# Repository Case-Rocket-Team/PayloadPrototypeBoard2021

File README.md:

This is a prototype board for the 2021 ESRA Payload. We are planning on developing a parafoil guided payload that will be ejected from the rocket at apogee, and guide itself to landing. 

Capabilities of this board include: 
  6 Servo Outputs
  4 External IO 
  High Acceleration Accelerometer (H3LIS331DLTR)
  9 Axis IMU (ICM-20948) 
  LORA Radio (RFM98) 
  Barometer (BMP388) 
  18V Max Input
  Battery Voltage Reader
  Various LEDs for status 

This board should be used on the scale test payload we are developing, and will be a proof of concept for the final ESRA payload we will develop after validating this design.

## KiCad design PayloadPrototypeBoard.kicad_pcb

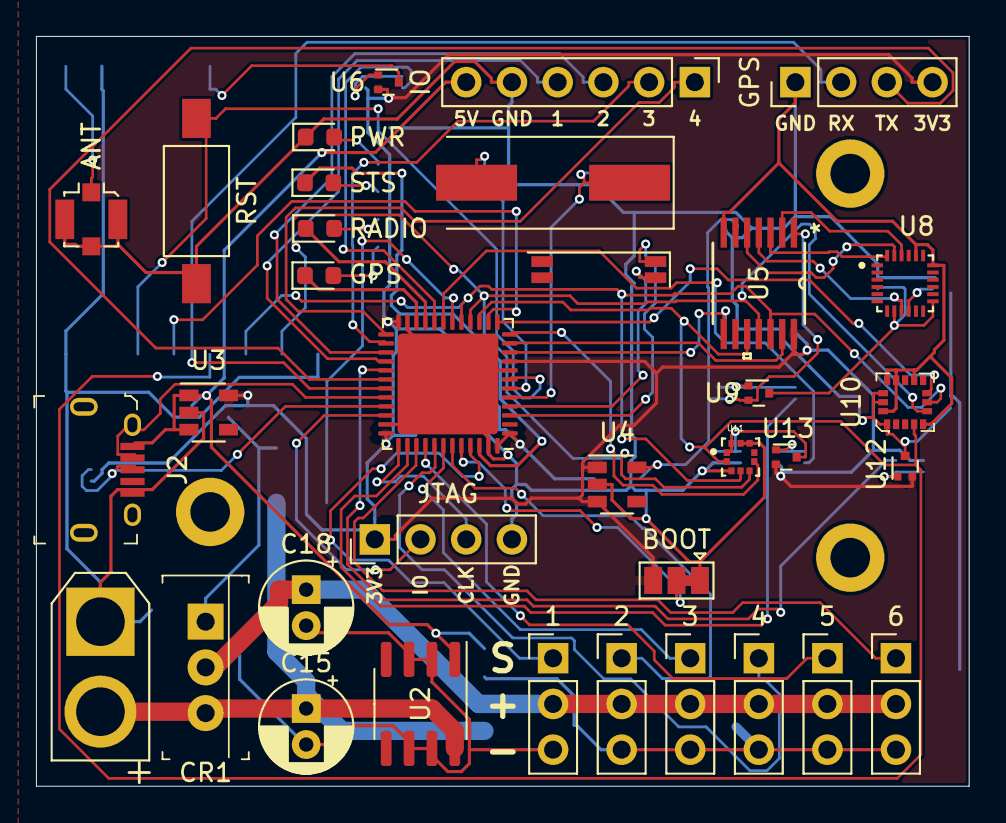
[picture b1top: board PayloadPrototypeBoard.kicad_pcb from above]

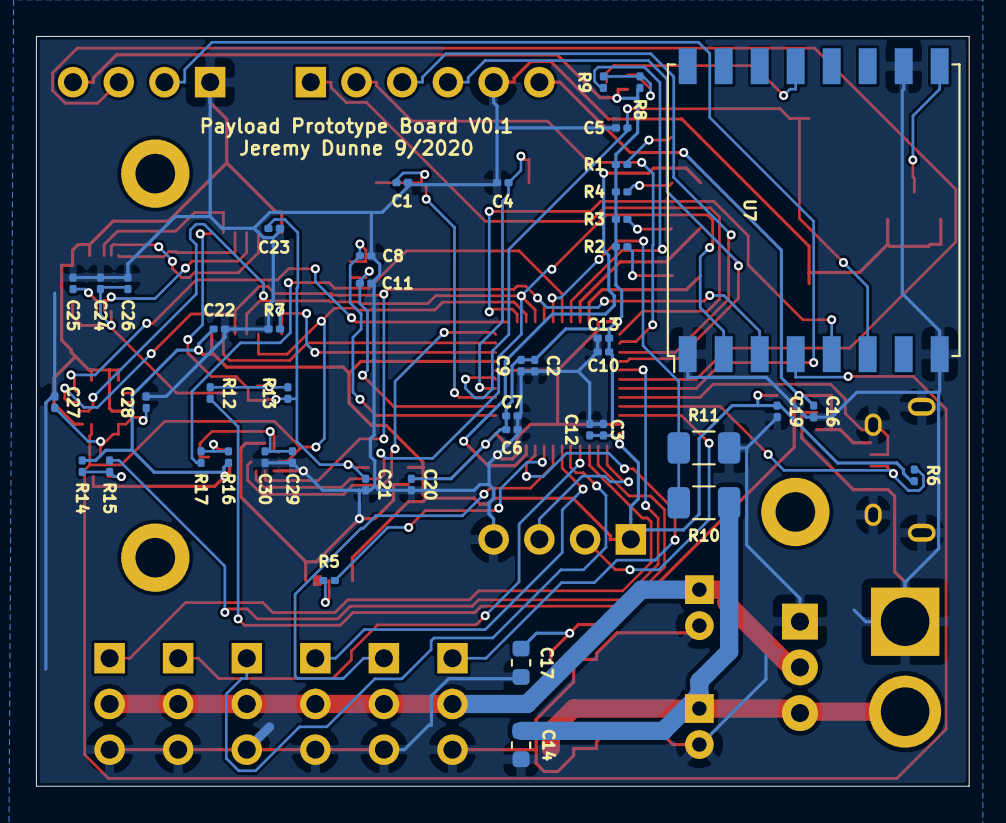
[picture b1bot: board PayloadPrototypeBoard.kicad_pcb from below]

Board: 2 copper layers, 51.8 x 41.7 mm, 84 parts (46 on the bottom side), 63 nets.

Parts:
1: SERVO 1; PinHeader_1x03_P2.54mm_Vertical
2: SERVO 2; PinHeader_1x03_P2.54mm_Vertical
3: SERVO 3; PinHeader_1x03_P2.54mm_Vertical
4: SERVO 4; PinHeader_1x03_P2.54mm_Vertical
5: SERVO 5; PinHeader_1x03_P2.54mm_Vertical
6: SERVO 6; PinHeader_1x03_P2.54mm_Vertical
ANT: Conn_Coaxial; U.FL_Molex_MCRF_73412-0110_Vertical
BOOT: BOOT0; SolderJumper-3_P1.3mm_Bridged12_Pad1.0x1.5mm
C1, C4: 20pF; C_0201_0603Metric
C2, C16, C19, C20, C21: 1uF; C_0201_0603Metric
C3: 10nF; C_0201_0603Metric
C5, C6, C9, C10, C12, C22, C23, C24, C25, C26, C29, C30: 0.1uF; C_0201_0603Metric
C7, C13: 4.7uF; C_0201_0603Metric
C8, C11: 10pF; C_0201_0603Metric
C14: 0.33uF; C_0603_1608Metric
C15, C18: 10uF; CP_Radial_D5.0mm_P2.00mm
C17: 0.1uF; C_0603_1608Metric
C27: 10uF; C_0201_0603Metric
C28: .1uF; C_0201_0603Metric
CR1: LD1085V50; TO-220-3
GPS: GPS_LOCK; LED_0603_1608Metric
GPS#2: GPS; PinHeader_1x04_P2.54mm_Vertical
H1, H2, H3: MountingHole; MountingHole_2.2mm_M2_DIN965_Pad
IO: EXTERNAL IO; PinHeader_1x06_P2.54mm_Vertical
J2: USB_OTG; USB_Micro_B_Female_10118194-0001LF
J9: PWR; AMASS_XT30U-F_1x02_P5.0mm_Vertical
JTAG: JTAG; PinHeader_1x04_P2.54mm_Vertical
PWR: PWR; LED_0603_1608Metric
R1, R2, R3, R4, R5, R7, R8, R9, R12, R13, R14, R15, R16, R17: 10K; R_0201_0603Metric
R6: 1.5K; R_0201_0603Metric
R10: 10K; R_1206_3216Metric
R11: 2.5k; R_1206_3216Metric
RADIO: RADIO_LOCK; LED_0603_1608Metric
RST: RESET; SW_SPST_FSMSM
STS: STATUS; LED_0603_1608Metric
U1: STM32F072C8Ux; QFN-48-1EP_7x7mm_P0.5mm_EP5.6x5.6mm
U2: L78L05_SO8; SOIC-8_3.9x4.9mm_P1.27mm
U3: MIC5504-3.3YM5; SOT-23-5
U4: MIC5504-1.8YM5; SOT-23-5
U5: TXS0104EPWR
U6, U9, U12, U13: SSM3J15FV; SOT-723
U7: RFM96W-433S2; HOPERF_RFM9XW_SMD
U8: ICM-20948; QFN40P300X300X105-24N
U10: H3LIS331DLTR; TFLGA-16_3x3mm
U11: BMP388; PQFN50P200X200X80-10N
Y1: 8MHz; Crystal_SMD_HC49-SD
Y2: 32Khz; Crystal_SMD_SeikoEpson_MC146-4Pin_6.7x1.5mm

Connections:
+1V8: C21.1, C23.2, R13.1, U4.5, U5.1, U9.2
+3V3: BOOT.3, C2.1, C3.1, C6.1, C7.1, C9.1, C10.1, C12.1, C13.1, C19.1, C20.1, C22.1, GPS#2.4, JTAG.1, R1.2, R2.2, R3.2, R4.2, R6.2, R8.2, R14.1, R16.2, U1.1, U1.9, U1.24, U1.36, U1.48, U3.5, U4.1, U4.3, U5.14, U6.2, U12.2, U13.2
+5V: C16.1, C17.1, IO.6, J2.1, U2.1, U3.1, U3.3
ACCEL_CS: U1.13, U10.8
ACCEL_EN: R15.1, U1.29
BARO_EN: R17.1, U1.19
BMP_CS: U1.12, U11.6
BOOT0: R5.2, U1.44
GND: 1.3, 2.3, 3.3, 4.3, 5.3, 6.3, ANT.2, BOOT.1, C1.2, C2.2, C3.2, C4.2, C5.2, C6.2, C7.2, C8.2, C9.2, C10.2, C11.2, C12.2, C13.2, C14.2, C15.2, C16.2, C17.2, C18.2, C19.2, C20.2, C21.2, C22.2, C23.1, C24.1, C25.1, C26.1, C27.2, C28.2, C29.1, C30.2, CR1.1, GPS#2.1, IO.5, J2.5, J2.SH, J9.1, JTAG.4, PWR.1, R7.1, R11.2, RST.1, U1.8, U1.23, U1.35, U1.47, U1.49, U2.2, U2.3, U2.6, U2.7, U3.2, U4.2, U5.7, U7.1, U7.8, U7.10, U8.18, U8.20, U10.5, U10.10, U10.12, U10.13, U10.16, U11.3, U11.8, U11.9
GPS_LOCK_LED: GPS.1, U1.22
GPS_RX: GPS#2.2, U1.31
GPS_TX: GPS#2.3, U1.30
IMU_CS: U1.11, U5.13
IMU_EN: R12.2, U1.38
IO_1: IO.4, U1.28
IO_2: IO.3, U1.27
IO_3: IO.2, U1.26
IO_4: IO.1, U1.25
MISO_3V3: U1.16, U5.11, U7.2, U10.6, U11.5
MOSI_3V3: U1.17, U5.12, U7.3, U10.7, U11.4
unnamed: C24.2, C26.2, U8.8, U8.13, U9.3
unnamed: C25.2, U8.10
unnamed: C27.1, C28.1, U10.1, U10.14, U10.15, U12.3
unnamed: C29.2, C30.1, U11.1, U11.10, U13.3
unnamed: PWR.2, R1.1
unnamed: GPS.2, R2.1
unnamed: R3.1, RADIO.2
unnamed: R4.1, STS.2
unnamed: ANT.1, U7.9
unnamed: BOOT.2, R5.1
unnamed: R8.1, R9.2, U6.1
unnamed: R12.1, R13.2, U9.1
unnamed: R14.2, R15.2, U12.1
unnamed: R16.1, R17.2, U13.1
unnamed: U5.2, U8.22
unnamed: U5.3, U8.24
unnamed: U5.4, U8.9
unnamed: U5.5, U8.23
unnamed: U6.3, U7.13
OE: R7.2, U1.10, U5.8
OSC32_IN: C8.1, U1.3, Y2.1
OSC32_OUT: C11.1, U1.4, Y2.4
OSC_IN: C1.1, U1.5, Y1.1
OSC_OUT: C4.1, U1.6, Y1.2
RADIO_CS: U1.14, U7.5
RADIO_EN: R9.1, U1.20
RADIO_LOCK_LED: RADIO.1, U1.21
RST: C5.1, RST.2, U1.7, U7.6
SCK_3V3: U1.15, U5.10, U7.4, U10.4, U11.2
SERVO_1: 1.1, U1.45
SERVO_2: 2.1, U1.43
SERVO_3: 3.1, U1.42
SERVO_4: 4.1, U1.41
SERVO_5: 5.1, U1.40
SERVO_6: 6.1, U1.39
SERVO_PWR: 1.2, 2.2, 3.2, 4.2, 5.2, 6.2, C18.1, CR1.2
STATUS_LED: STS.1, U1.46
SWCLK: JTAG.3, U1.37
SWDIO: JTAG.2, U1.34
USB_DM: J2.2, U1.32
USB_DP: J2.3, R6.1, U1.33
VIN: C14.1, C15.1, CR1.3, J9.2, R10.1, U2.8
VOLTAGE_READ: R10.2, R11.1, U1.18

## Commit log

2020-09-17 finished board
2020-09-17 fixed symbol issues

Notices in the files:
parts and their libraries:
Copyright 2016 Accelerated Designs. All rights reserved.
